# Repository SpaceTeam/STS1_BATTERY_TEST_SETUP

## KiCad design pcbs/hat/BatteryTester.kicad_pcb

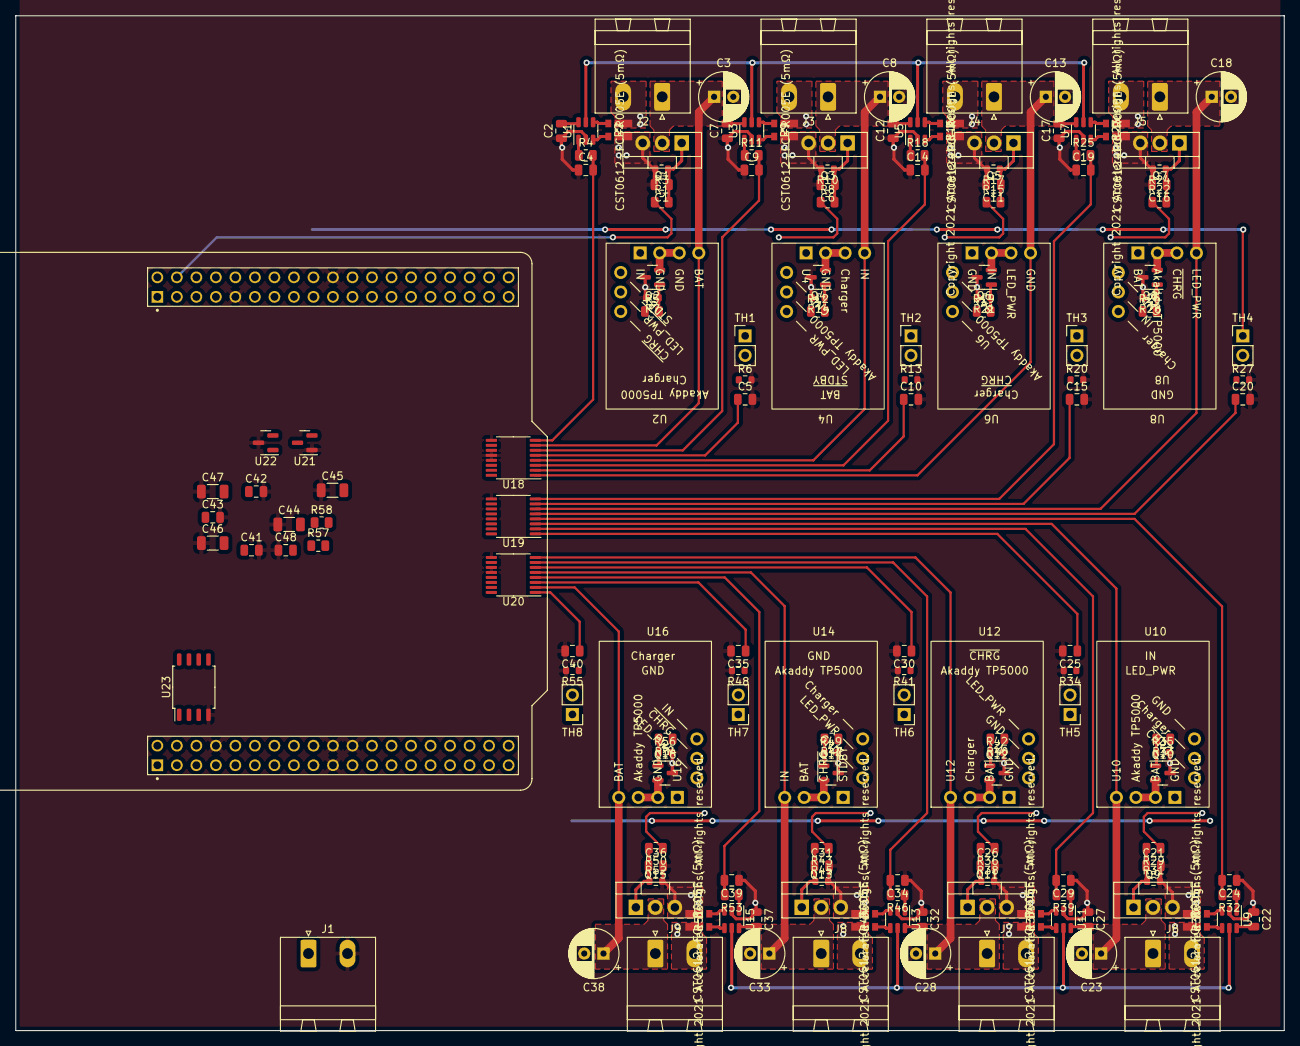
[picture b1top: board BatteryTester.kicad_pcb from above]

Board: 4 copper layers, 165.1 x 132.1 mm, 162 parts (0 on the bottom side), 118 nets.

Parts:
C1, C6, C11, C16, C21, C26, C31, C36: 220n; C_0805_2012Metric
C2, C7, C12, C17, C22, C27, C32, C37, C41, C42, C43, C48: 100n; C_0805_2012Metric
C3, C8, C13, C18, C23, C28, C33, C38: optional; CP_Radial_D6.3mm_P2.50mm
C4, C9, C14, C19, C24, C29, C34, C39: 15u; C_0805_2012Metric
C5, C10, C15, C20, C25, C30, C35, C40: 1u; C_0805_2012Metric
C44, C45: 47u; C_1206_3216Metric
C46, C47: 22u; C_1206_3216Metric
J1: Supply Connector; PhoenixContact_MSTBA_2,5_2-G-5,08_1x02_P5.08mm_Horizontal
J2, J3, J4, J5, J6, J7, J8, J9: Battery Connector; PhoenixContact_MSTBA_2,5_2-G-5,08_1x02_P5.08mm_Horizontal
Q1, Q3, Q5, Q7, Q9, Q11, Q13, Q15: DMT6009LCT; TO-220-3_Vertical
Q2, Q4, Q6, Q8, Q10, Q12, Q14, Q16: AO3414; SOT-23
R1, R5, R8, R12, R15, R19, R22, R26, R29, R33, R36, R40, R43, R47, R50, R54: 680; R_0805_2012Metric
R2, R9, R16, R23, R30, R37, R44, R51: CST0612-FC-R005E (5mΩ); CST0612-FC-R002E
R3, R6, R7, R10, R13, R14, R17, R20, R21, R24, R27, R28, R31, R34, R35, R38, R41, R42, R45, R48, R49, R52, R55, R56: 10k; R_0603_1608Metric
R4, R11, R18, R25, R32, R39, R46, R53: 1k; R_0805_2012Metric
R57, R58: 100; R_0805_2012Metric
TH1, TH2, TH3, TH4, TH5, TH6, TH7, TH8: Thermistor_NTC_10k; PinHeader_1x02_P2.54mm_Vertical
U1, U3, U5, U7, U9, U11, U13, U15: INA181A2IDBVR; SOT-23-6
U2, U4, U6, U8, U10, U12, U14, U16: TP5000_Breakout_Akaddy
U17: NUCLEO-F401RE; ST_Morpho_Connector_64
U18, U19, U20: ADS7828; TSSOP-16_4.4x5mm_P0.65mm
U21: AP2138N-2.5TRG1; SOT-23
U22: LM3480-5.0; SOT-23
U23: SST25VF016B; SOIC-8_5.275x5.275mm_P1.27mm

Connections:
+3V3: C48.2, U23.3 (~WP), U23.7 (~HOLD), U23.8 (VDD)
+5V: C2.2, C7.2, C12.2, C17.2, C22.2, C27.2, C32.2, C37.2, C41.1, C42.1, C43.1, R57.1, TH1.1, TH2.1, TH3.1, TH4.1, TH5.1, TH6.1, TH7.1, TH8.1, U1.6 (V+), U3.6 (V+), U5.6 (V+), U7.6 (V+), U9.6 (V+), U11.6 (V+), U13.6 (V+), U15.6 (V+), U17.CN7_16 (+3V3_S1), U18.16 (VDD), U19.12 (A0), U19.16 (VDD), U20.13 (A1), U20.16 (VDD)
/Board/ADC_SCL: U17.CN10_3 (PB8), U18.14 (SCL), U19.14 (SCL), U20.14 (SCL)
/Board/ADC_SDA: U17.CN10_5 (PB9), U18.15 (SDA), U19.15 (SDA), U20.15 (SDA)
/Board/MEM_MISO: U17.CN7_2 (PC11), U23.2 (SO)
/Board/MEM_MOSI: U17.CN7_3 (PC12), U23.5 (SI)
/Board/MEM_SCK: U17.CN7_1 (PC10), U23.6 (SCK)
/Board/~MEM_CE: U17.CN7_4 (PD2), U23.1 (~CE)
/Converters/ADC_Ref: C47.2, U18.10 (REF), U19.10 (REF), U20.10 (REF), U22.1 (VO)
/SENSOR_10: C3.1, J2.1, Q1.2 (D), U2.3 (OUT+), U18.7 (CH6)
/SENSOR_11: C4.2, R4.2, U18.8 (CH7)
/SENSOR_12: C5.1, R6.1, TH1.2, U18.5 (CH4)
/SENSOR_13: U2.11 (~STDBY), U17.CN10_2 (PC8)
/SENSOR_20: C8.1, J3.1, Q3.2 (D), U4.3 (OUT+), U18.4 (CH3)
/SENSOR_21: C9.2, R11.2, U18.6 (CH5)
/SENSOR_22: C10.1, R13.1, TH2.2, U18.2 (CH1)
/SENSOR_23: U4.11 (~STDBY), U17.CN10_6 (PC5)
/SENSOR_30: C13.1, J4.1, Q5.2 (D), U6.3 (OUT+), U18.1 (CH0)
/SENSOR_31: C14.2, R18.2, U18.3 (CH2)
/SENSOR_32: C15.1, R20.1, TH3.2, U19.7 (CH6)
/SENSOR_33: U6.11 (~STDBY), U17.CN10_34 (PC4)
/SENSOR_40: C18.1, J5.1, Q7.2 (D), U8.3 (OUT+), U19.6 (CH5)
/SENSOR_41: C19.2, R25.2, U19.8 (CH7)
/SENSOR_42: C20.1, R27.1, TH4.2, U19.5 (CH4)
/SENSOR_43: U8.11 (~STDBY), U17.CN10_29 (PB5)
/SENSOR_50: C23.1, J6.1, Q9.2 (D), U10.3 (OUT+), U19.3 (CH2)
/SENSOR_51: C24.2, R32.2, U19.4 (CH3)
/SENSOR_52: C25.1, R34.1, TH5.2, U19.1 (CH0)
/SENSOR_53: U10.11 (~STDBY), U17.CN10_25 (PB10)
/SENSOR_60: C28.1, J7.1, Q11.2 (D), U12.3 (OUT+), U20.8 (CH7)
/SENSOR_61: C29.2, R39.2, U19.2 (CH1)
/SENSOR_62: C30.1, R41.1, TH6.2, U20.6 (CH5)
/SENSOR_63: U12.11 (~STDBY), U17.CN10_21 (PA9)
/SENSOR_70: C33.1, J8.1, Q13.2 (D), U14.3 (OUT+), U20.5 (CH4)
/SENSOR_71: C34.2, R46.2, U20.7 (CH6)
/SENSOR_72: C35.1, R48.1, TH7.2, U20.3 (CH2)
/SENSOR_73: U14.11 (~STDBY), U17.CN7_36 (PC1/PB9)
/SENSOR_80: C38.1, J9.1, Q15.2 (D), U16.3 (OUT+), U20.2 (CH1)
/SENSOR_81: C39.2, R53.2, U20.4 (CH3)
/SENSOR_82: C40.1, R55.1, TH8.2, U20.1 (CH0)
/SENSOR_83: U16.11 (~STDBY), U17.CN7_37 (PC3)
/SIGNAL_10: R5.1, U17.CN10_12 (PA12)
/SIGNAL_11: R1.1, U17.CN10_4 (PC6)
/SIGNAL_20: R12.1, U17.CN10_16 (PB12)
/SIGNAL_21: R8.1, U17.CN10_24 (PB1)
/SIGNAL_30: R19.1, U17.CN10_33 (PA10)
/SIGNAL_31: R15.1, U17.CN10_30 (PB13)
/SIGNAL_40: R26.1, U17.CN10_28 (PB14)
/SIGNAL_41: R22.1, U17.CN10_27 (PB4)
/SIGNAL_50: R33.1, U17.CN10_23 (PA8)
/SIGNAL_51: R29.1, U17.CN10_22 (PB2)
/SIGNAL_60: R40.1, U17.CN10_19 (PC7)
/SIGNAL_61: R36.1, U17.CN10_17 (PB6)
/SIGNAL_70: R47.1, U17.CN7_38 (PC0/PB8)
/SIGNAL_71: R43.1, U17.CN7_30 (PA1)
/SIGNAL_80: R54.1, U17.CN7_35 (PC2)
/SIGNAL_81: R50.1, U17.CN7_28 (PA0)
/test-battery-1/GNDBAT: J2.2, R2.4
/test-battery-2/GNDBAT: J3.2, R9.4
/test-battery-3/GNDBAT: J4.2, R16.4
/test-battery-4/GNDBAT: J5.2, R23.4
/test-battery-5/GNDBAT: J6.2, R30.4
/test-battery-6/GNDBAT: J7.2, R37.4
/test-battery-7/GNDBAT: J8.2, R44.4
/test-battery-8/GNDBAT: J9.2, R51.4
GND: C1.2, C2.1, C3.2, C4.1, C5.2, C6.2, C7.1, C8.2, C9.1, C10.2, C11.2, C12.1, C13.2, C14.1, C15.2, C16.2, C17.1, C18.2, C19.1, C20.2, C21.2, C22.1, C23.2, C24.1, C25.2, C26.2, C27.1, C28.2, C29.1, C30.2, C31.2, C32.1, C33.2, C34.1, C35.2, C36.2, C37.1, C38.2, C39.1, C40.2, C41.2, C42.2, C43.2, C44.1, C45.1, C46.1, C47.1, C48.1, J1.2, Q1.3 (S), Q2.3 (S), Q3.3 (S), Q4.3 (S), Q5.3 (S), Q6.3 (S), Q7.3 (S), Q8.3 (S), Q9.3 (S), Q10.3 (S), Q11.3 (S), Q12.3 (S), Q13.3 (S), Q14.3 (S), Q15.3 (S), Q16.3 (S), R2.1, R3.2, R6.2, R7.2, R9.1, R10.2, R13.2, R14.2, R16.1, R17.2, R20.2, R21.2, R23.1, R24.2, R27.2, R28.2, R30.1, R31.2, R34.2, R35.2, R37.1, R38.2, R41.2, R42.2, R44.1, R45.2, R48.2, R49.2, R51.1, R52.2, R55.2, R56.2, U1.2 (GND), U3.2 (GND), U5.2 (GND), U7.2 (GND), U9.2 (GND), U11.2 (GND), U13.2 (GND), U15.2 (GND), U17.CN7_8 (GND_S1), U17.CN7_19 (GND_S1), U17.CN7_20 (GND_S1), U17.CN7_22 (GND_S1), U17.CN10_9 (GND_S2), U17.CN10_20 (GND_S2), U18.9 (GND), U18.11 (COM), U18.12 (A0), U18.13 (A1), U19.9 (GND), U19.11 (COM), U19.13 (A1), U20.9 (GND), U20.11 (COM), U20.12 (A0), U21.1 (GND), U22.3 (GND), U23.4 (VSS)
unnamed: C1.1, Q1.1 (G), R1.2, R3.1
unnamed: C6.1, Q3.1 (G), R8.2, R10.1
unnamed: C11.1, Q5.1 (G), R15.2, R17.1
unnamed: C16.1, Q7.1 (G), R22.2, R24.1
unnamed: C21.1, Q9.1 (G), R29.2, R31.1
unnamed: C26.1, Q11.1 (G), R36.2, R38.1
unnamed: C31.1, Q13.1 (G), R43.2, R45.1
unnamed: C36.1, Q15.1 (G), R50.2, R52.1
unnamed: C44.2, R57.2, U21.3 (VI)
unnamed: C45.2, R58.2, U22.2 (VI)
unnamed: Q2.1 (G), R5.2, R7.1
unnamed: Q2.2 (D), U2.2 (GND), U2.4 (GND)
unnamed: Q4.1 (G), R12.2, R14.1
unnamed: Q4.2 (D), U4.2 (GND), U4.4 (GND)
unnamed: Q6.1 (G), R19.2, R21.1
unnamed: Q6.2 (D), U6.2 (GND), U6.4 (GND)
unnamed: Q8.1 (G), R26.2, R28.1
unnamed: Q8.2 (D), U8.2 (GND), U8.4 (GND)
unnamed: Q10.1 (G), R33.2, R35.1
unnamed: Q10.2 (D), U10.2 (GND), U10.4 (GND)
unnamed: Q12.1 (G), R40.2, R42.1
unnamed: Q12.2 (D), U12.2 (GND), U12.4 (GND)
unnamed: Q14.1 (G), R47.2, R49.1
unnamed: Q14.2 (D), U14.2 (GND), U14.4 (GND)
unnamed: Q16.1 (G), R54.2, R56.1
unnamed: Q16.2 (D), U16.2 (GND), U16.4 (GND)
unnamed: R2.2, U1.3 (+)
unnamed: R2.3, U1.4 (-)
unnamed: R4.1, U1.1
unnamed: R9.2, U3.3 (+)
unnamed: R9.3, U3.4 (-)
unnamed: R11.1, U3.1
unnamed: R16.2, U5.3 (+)
unnamed: R16.3, U5.4 (-)
unnamed: R18.1, U5.1
unnamed: R23.2, U7.3 (+)
unnamed: R23.3, U7.4 (-)
unnamed: R25.1, U7.1
unnamed: R30.2, U9.3 (+)
unnamed: R30.3, U9.4 (-)
unnamed: R32.1, U9.1
unnamed: R37.2, U11.3 (+)
unnamed: R37.3, U11.4 (-)
unnamed: R39.1, U11.1
unnamed: R44.2, U13.3 (+)
unnamed: R44.3, U13.4 (-)
unnamed: R46.1, U13.1
unnamed: R51.2, U15.3 (+)
unnamed: R51.3, U15.4 (-)
unnamed: R53.1, U15.1
VCC: J1.1, R58.1, U2.1 (IN+), U4.1 (IN+), U6.1 (IN+), U8.1 (IN+), U10.1 (IN+), U12.1 (IN+), U14.1 (IN+), U16.1 (IN+), U17.CN7_24 (VIN_S1)
Vref_I_SENS: C46.2, U1.5 (REF), U3.5 (REF), U5.5 (REF), U7.5 (REF), U9.5 (REF), U11.5 (REF), U13.5 (REF), U15.5 (REF), U21.2 (VO)

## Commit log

2022-08-12 init
2022-08-12 add kicad libraries
2022-08-12 cleanup
2022-08-12 remove kicad backups
2022-08-15 setup hierarchy and add Nucleo footprint
2022-08-15 change libs submodule branch to eps_additions
2022-08-15 remove unnecessary files
2022-08-15 update gitignore
2022-08-15 fix symbol and footprint libraries
2022-08-15 add ADCs
2022-08-20 select parts for current and temperature sensors
2022-08-20 work on charging circuit
2022-09-04 more work on charging circuit
2022-09-04 fix the current sensor
2022-09-05 change ADCs and connect all Sensors and Signals
2022-09-05 formatting
2022-09-05 add discharge sims
2022-09-05 add vref for adc's
2022-09-18 few little change
2022-09-18 add memory + check footprints
2022-09-19 beginning of the layout
2022-10-16 finish the pin assignment
2022-10-16 reassign adc's
2022-10-17 pcb layout progress
2022-11-05 add basic firmware to send and receive data via usb
2022-11-05 create the basic project directory structure
2022-11-19 add serialization for transmission
2022-11-21 remove build warning from board
2022-11-21 add serial port test
    Cargo.lock also includes changes for the next commit
2022-12-05 implement the transmission protocol
2022-12-06 test the transmission protocol on the board
2022-12-07 send msg from board + setup panic handler
2022-12-08 read adc
2022-12-19 basic client ui + handle transmission errors
2022-12-20 move panic handler to own file + fix warnings
2022-12-20 move MsgTypes to firmware
2022-12-20 sample the adc
2023-03-02 some work on the firmware
2023-03-02 WIP (abstracting logic from hardware)

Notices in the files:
parts and their libraries:
Copyright 2021 Accelerated Designs. All rights reserved.
